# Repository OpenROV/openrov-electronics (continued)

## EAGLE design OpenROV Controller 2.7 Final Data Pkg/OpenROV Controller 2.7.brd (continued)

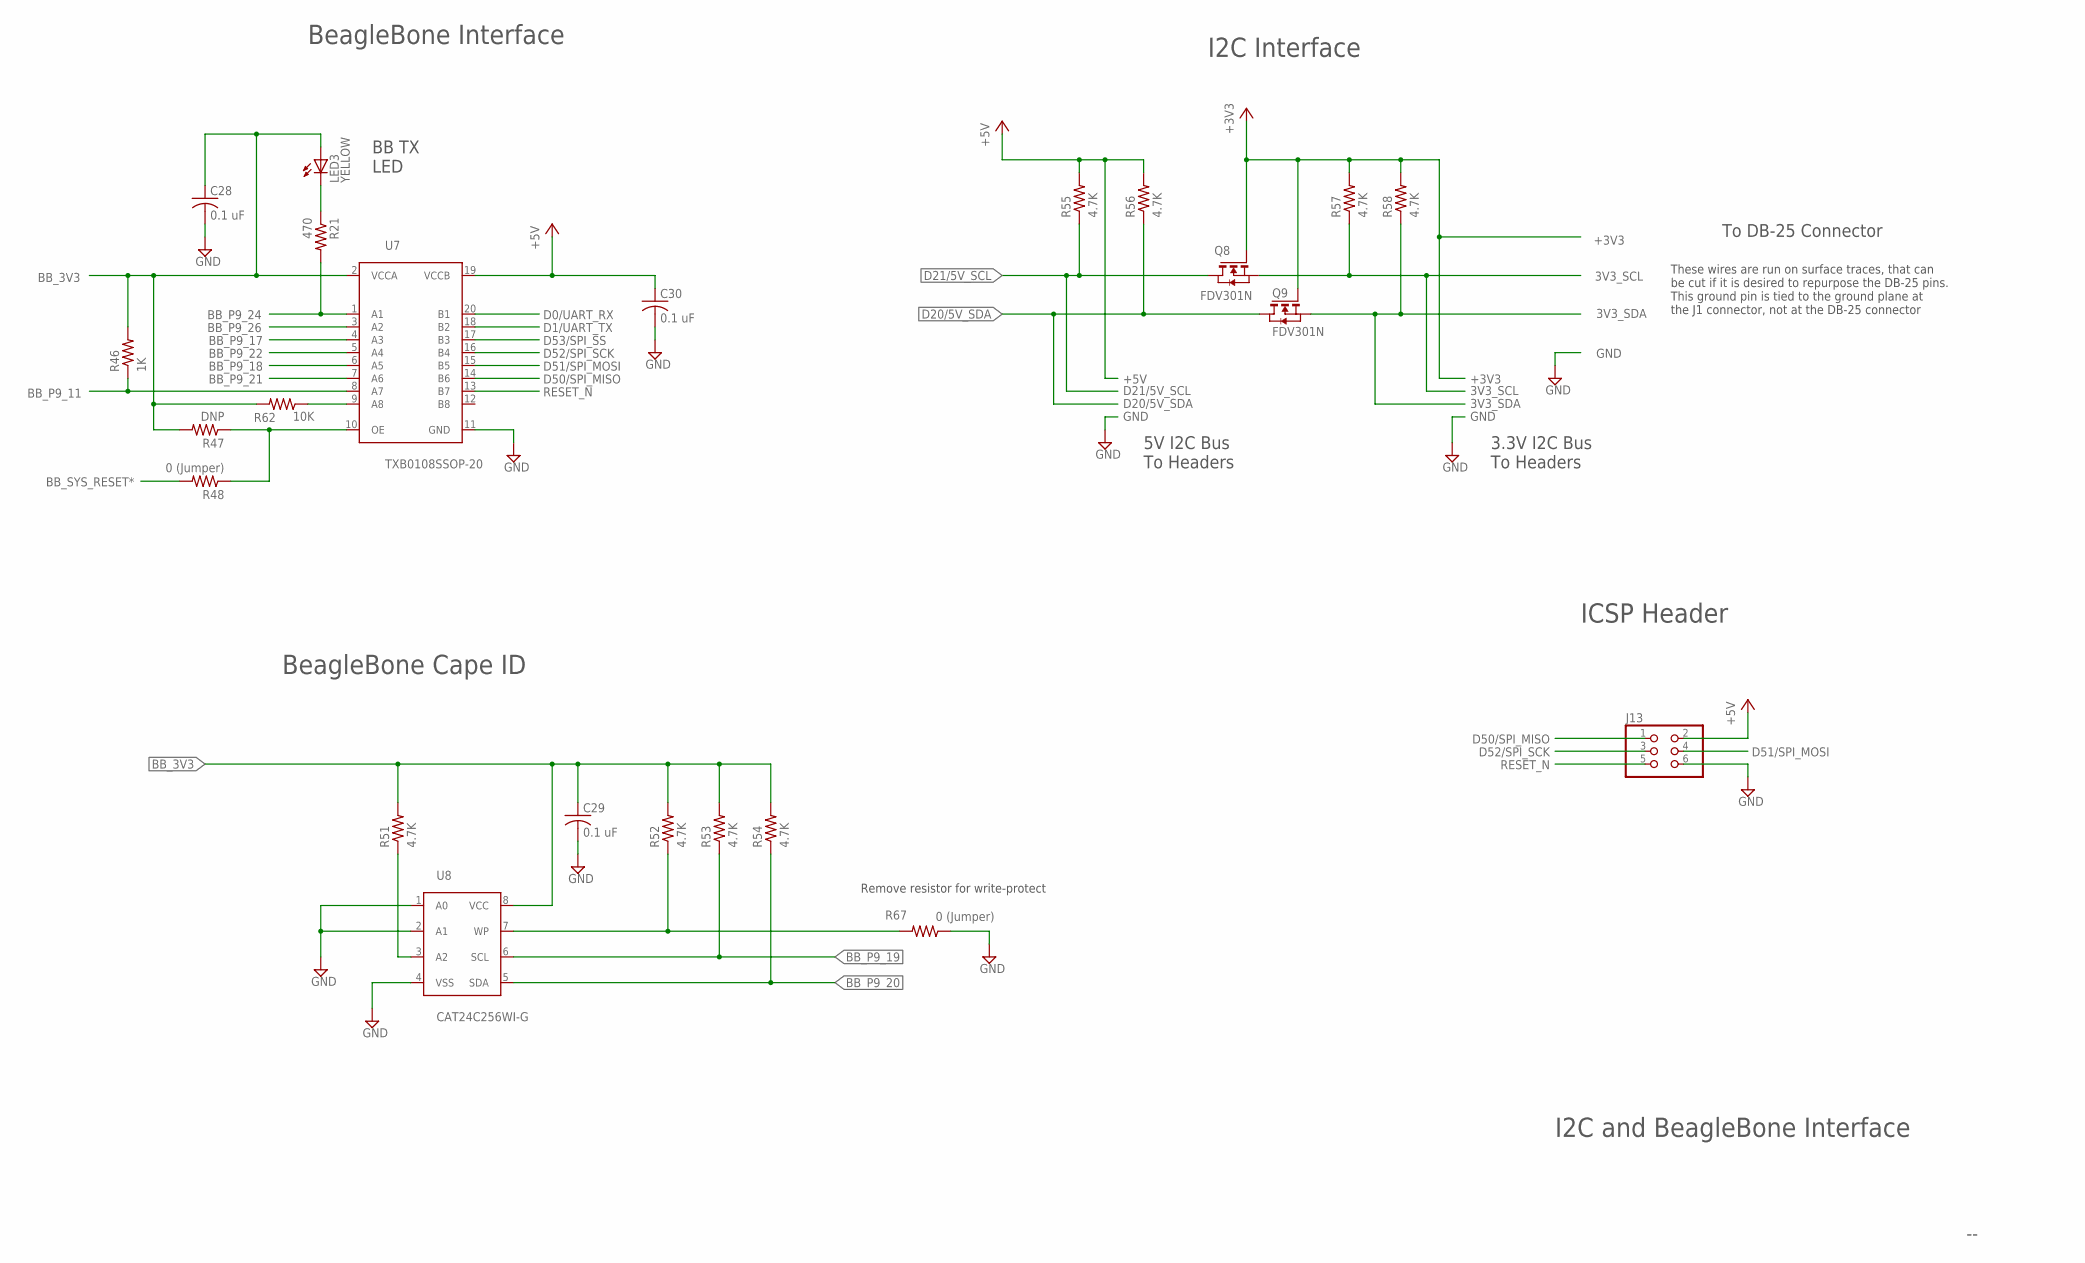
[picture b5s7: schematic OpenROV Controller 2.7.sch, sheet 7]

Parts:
C28, C29, C30: 0.1 uF; R0603
J13: HDR_PINS_2X3
LED3: YELLOW; LED_CHIPLED_0603
Q8, Q9: FDV301N; SOT23
R21: 470; R0603
R46: 1K; R0603
R47: DNP; R0603
R48, R67: 0 (Jumper); R0603
R51, R52, R53, R54, R55, R56, R57, R58: 4.7K; R0603
R62: 10K; R0603
U7: TXB0108SSOP-20; SSOP-20
U8: CAT24C256WI-G; SO8

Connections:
3V3_SCL: Q8.2 (S), R57.1; also elsewhere on the board
3V3_SDA: Q9.2 (S), R58.1; also elsewhere on the board
+3V3: Q8.1 (G), Q9.1 (G), R57.2, R58.2; also elsewhere on the board
+5V: C30.1, J13.2, R55.2, R56.2, U7.19 (VCCB); also elsewhere on the board
BB_3V3: C28.1, C29.1, LED3.A, R46.2, R47.2, R51.2, R52.2, R53.2, R54.2, R62.2, U7.2 (VCCA), U8.8 (VCC); also elsewhere on the board
BB_P9_11: R46.1, U7.8 (A7); also elsewhere on the board
BB_P9_17: U7.4 (A3); also elsewhere on the board
BB_P9_18: U7.6 (A5); also elsewhere on the board
BB_P9_19: R53.1, U8.6 (SCL); also elsewhere on the board
BB_P9_20: R54.1, U8.5 (SDA); also elsewhere on the board
BB_P9_21: U7.7 (A6); also elsewhere on the board
BB_P9_22: U7.5 (A4); also elsewhere on the board
BB_P9_24: R21.2, U7.1 (A1); also elsewhere on the board
BB_P9_26: U7.3 (A2); also elsewhere on the board
BB_SYS_RESET*: R48.2; also elsewhere on the board
D0/UART_RX: U7.20 (B1); also elsewhere on the board
D1/UART_TX: U7.18 (B2); also elsewhere on the board
D20/5V_SDA: Q9.3 (D), R56.1; also elsewhere on the board
D21/5V_SCL: Q8.3 (D), R55.1; also elsewhere on the board
D50/SPI_MISO: J13.1, U7.14 (B6); also elsewhere on the board
D51/SPI_MOSI: J13.4, U7.15 (B5); also elsewhere on the board
D52/SPI_SCK: J13.3, U7.16 (B4); also elsewhere on the board
D53/SPI_SS: U7.17 (B3); also elsewhere on the board
GND: C28.2, C29.2, C30.2, J13.6, R67.1, U7.11 (GND), U8.1 (A0), U8.2 (A1), U8.4 (VSS); also elsewhere on the board
unnamed: R47.1, R48.1, U7.10 (OE)
unnamed: R52.1, R67.2, U8.7 (WP)
unnamed: R51.1, U8.3 (A2)
unnamed: LED3.C, R21.1
unnamed: R62.1, U7.9 (A8)
RESET_N: J13.5, U7.13 (B7); also elsewhere on the board

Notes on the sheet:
I2C and BeagleBone Interface
I2C Interface
5V I2C Bus To Headers
3.3V I2C Bus To Headers
BeagleBone Interface
BeagleBone Cape ID
To DB-25 Connector
ICSP Header
These wires are run on surface traces, that can be cut if it is desired to repurpose the DB-25 pins. This ground pin is tied to the ground plane at the J1 connector, not at the DB-25 connector
Remove resistor for write-protect
BB TX LED

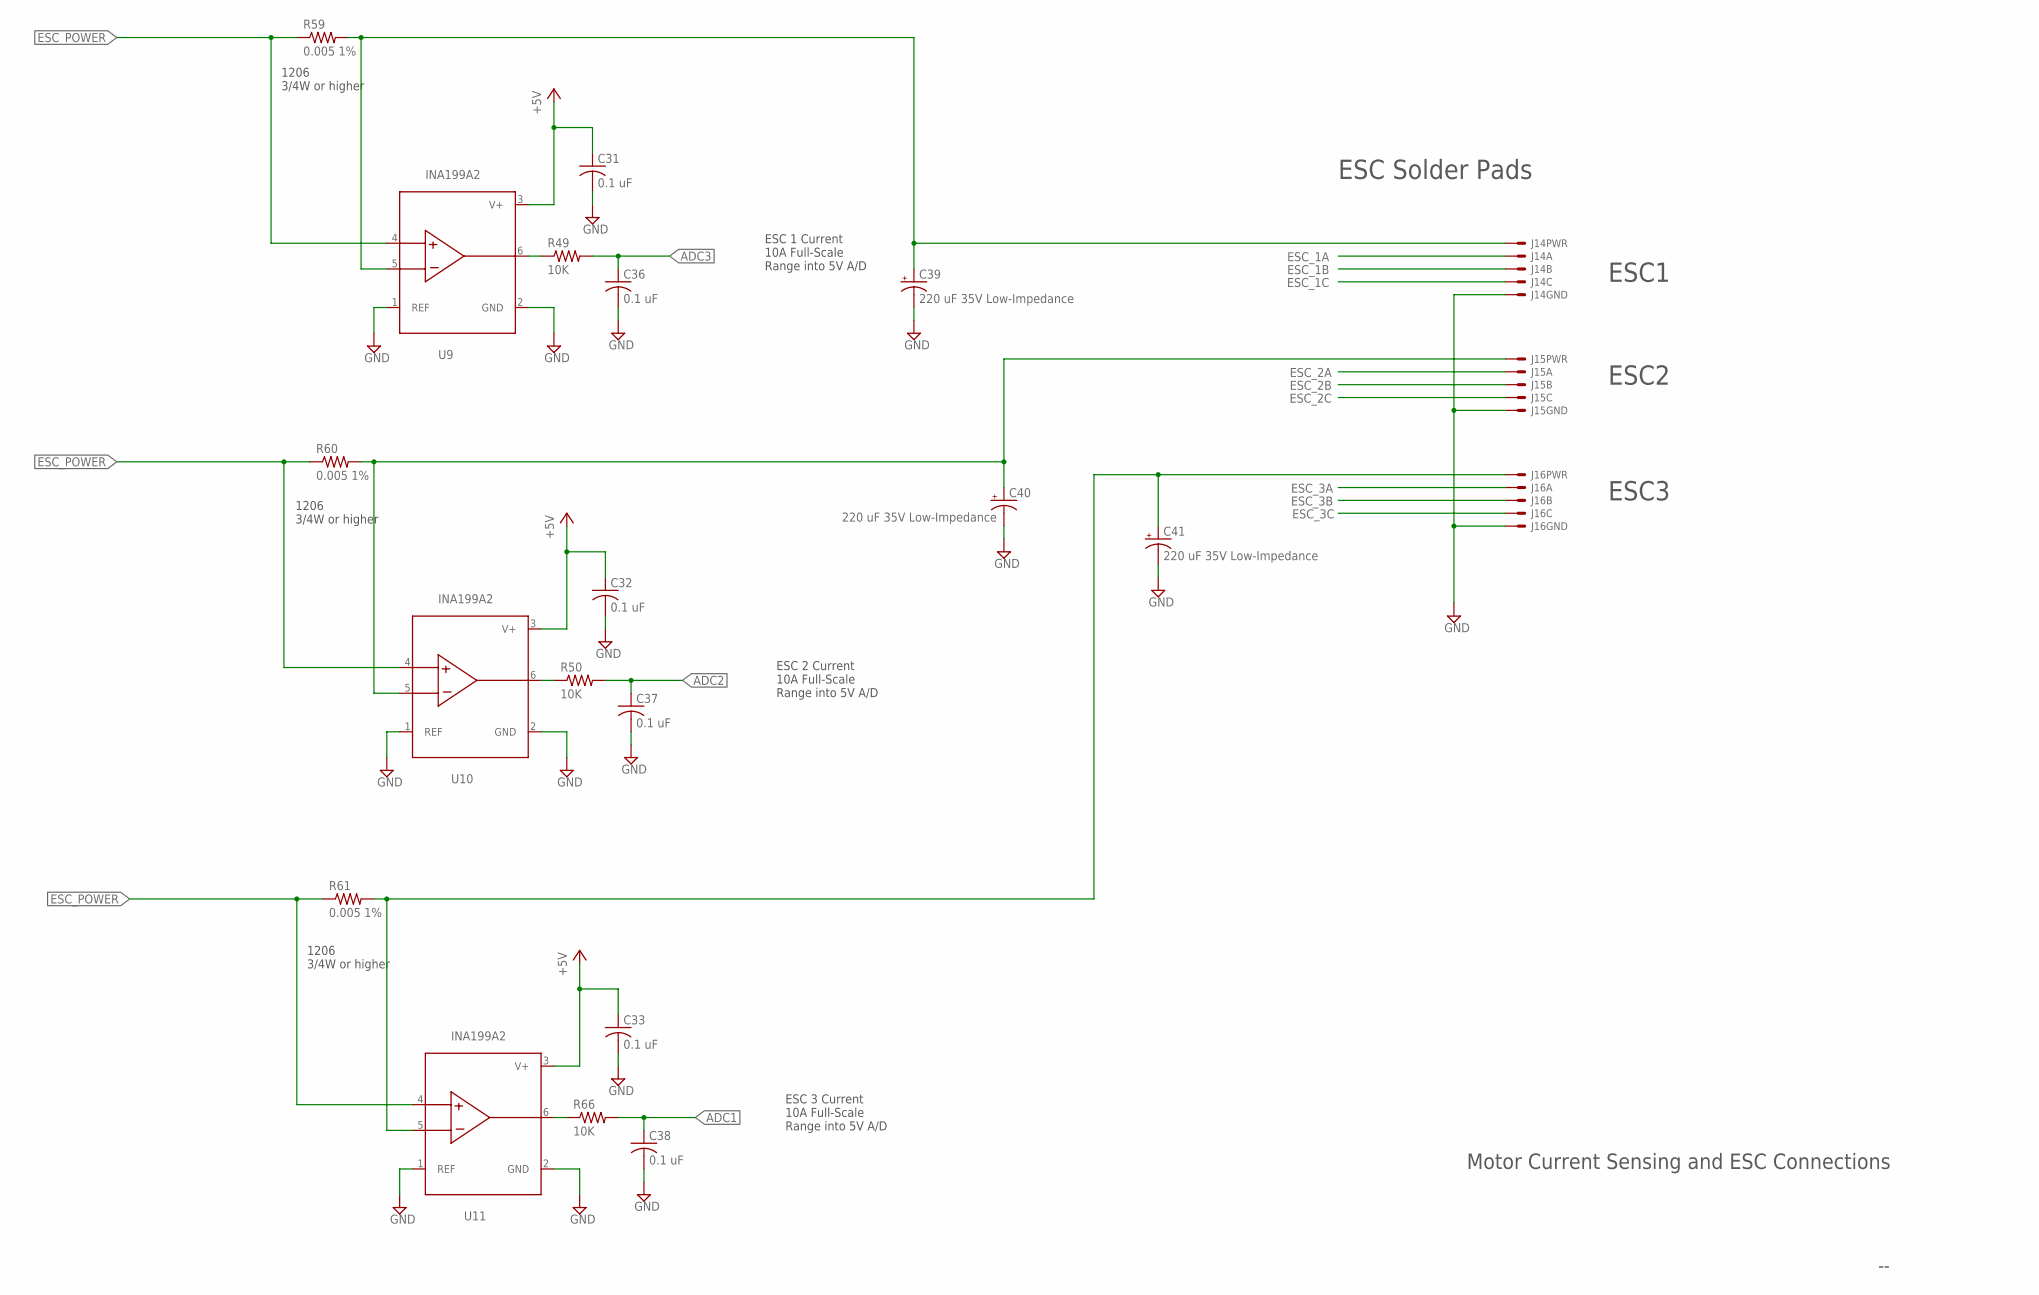
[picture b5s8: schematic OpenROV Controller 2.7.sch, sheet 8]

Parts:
C31, C32, C33, C36, C37, C38: 0.1 uF; R0603
C39, C40, C41: 220 uF 35V Low-Impedance; NICHICON_10MM
J14: ESC_PADS-AFRO-12/20A-ESC1; AFRO-ESC-12/20A-ESC1
J15: ESC_PADS-AFRO-12/20A-ESC2; AFRO-ESC-12/20A-ESC2
J16: ESC_PADS-AFRO-12/20A-ESC3; AFRO-ESC-12/20A-ESC3
R49, R50, R66: 10K; R0603
R59, R60, R61: 0.005 1%; R1206
U9, U10, U11: INA199A2; SC70-6L

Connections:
+5V: C31.1, C32.1, C33.1, U9.3 (V+), U10.3 (V+), U11.3 (V+); also elsewhere on the board
ADC1: C38.1, R66.2; also elsewhere on the board
ADC2: C37.1, R50.2; also elsewhere on the board
ADC3: C36.1, R49.2; also elsewhere on the board
ESC1_PWR: C39.+, J14.PWR1, J14.PWR2, R59.2, U9.5 (IN-)
ESC_1A: J14.A1, J14.A2; also elsewhere on the board
ESC_1B: J14.B1, J14.B2; also elsewhere on the board
ESC_1C: J14.C1, J14.C2; also elsewhere on the board
ESC_2A: J15.A1, J15.A2; also elsewhere on the board
ESC_2B: J15.B1, J15.B2; also elsewhere on the board
ESC_2C: J15.C1, J15.C2; also elsewhere on the board
ESC_3A: J16.A1, J16.A2; also elsewhere on the board
ESC_3B: J16.B1, J16.B2; also elsewhere on the board
ESC_3C: J16.C1, J16.C2; also elsewhere on the board
ESC_POWER: R59.1, R60.1, R61.1, U9.4 (IN+), U10.4 (IN+), U11.4 (IN+); also elsewhere on the board
ESC_PWR2: C40.+, J15.PWR1, J15.PWR2, R60.2, U10.5 (IN-)
ESC_PWR3: C41.+, J16.PWR1, J16.PWR2, R61.2, U11.5 (IN-)
GND: C31.2, C32.2, C33.2, C36.2, C37.2, C38.2, C39.-, C40.-, C41.-, J14.GND1, J14.GND2, J15.GND1, J15.GND2, J16.GND1, J16.GND2, U9.1 (REF), U9.2 (GND), U10.1 (REF), U10.2 (GND), U11.1 (REF), U11.2 (GND); also elsewhere on the board
unnamed: R49.1, U9.6 (VOUT)
unnamed: R50.1, U10.6 (VOUT)
unnamed: R66.1, U11.6 (VOUT)

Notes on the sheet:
Motor Current Sensing and ESC Connections
ESC Solder Pads
ESC1
ESC2
ESC3
1206 3/4W or higher
ESC 2 Current 10A Full-Scale Range into 5V A/D
ESC 1 Current 10A Full-Scale Range into 5V A/D
ESC 3 Current 10A Full-Scale Range into 5V A/D

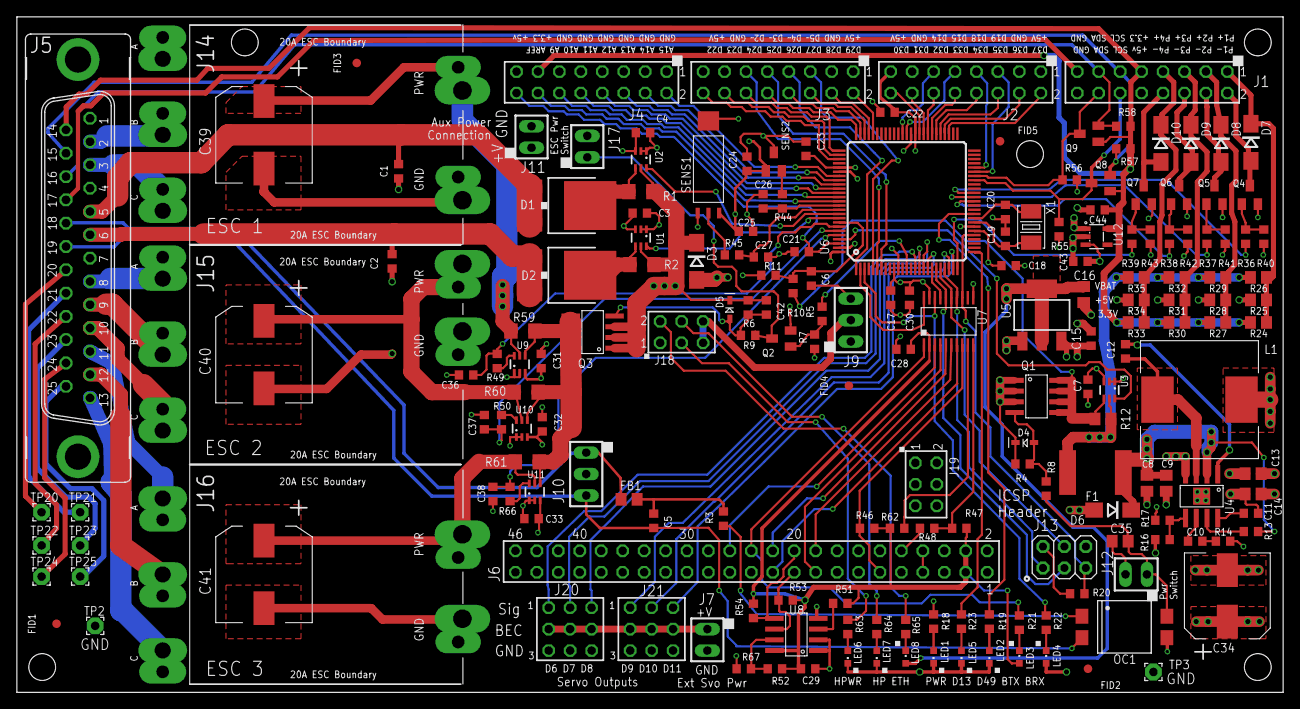
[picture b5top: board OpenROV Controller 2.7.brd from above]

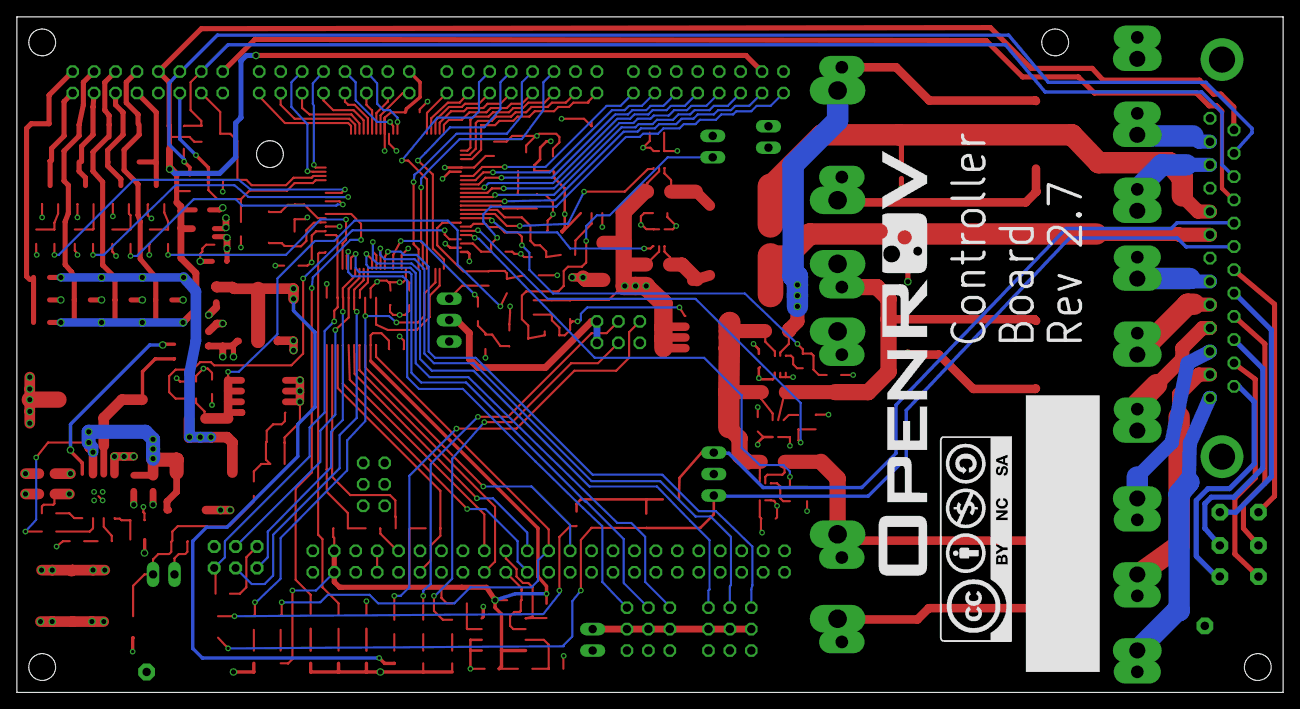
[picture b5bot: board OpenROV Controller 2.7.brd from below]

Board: 4 copper layers, 150.0 x 80.0 mm, 191 parts (2 on the bottom side), 159 nets.

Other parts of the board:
U$1: OROV-LOGO-2.00
U$2: CC-LOGO-1

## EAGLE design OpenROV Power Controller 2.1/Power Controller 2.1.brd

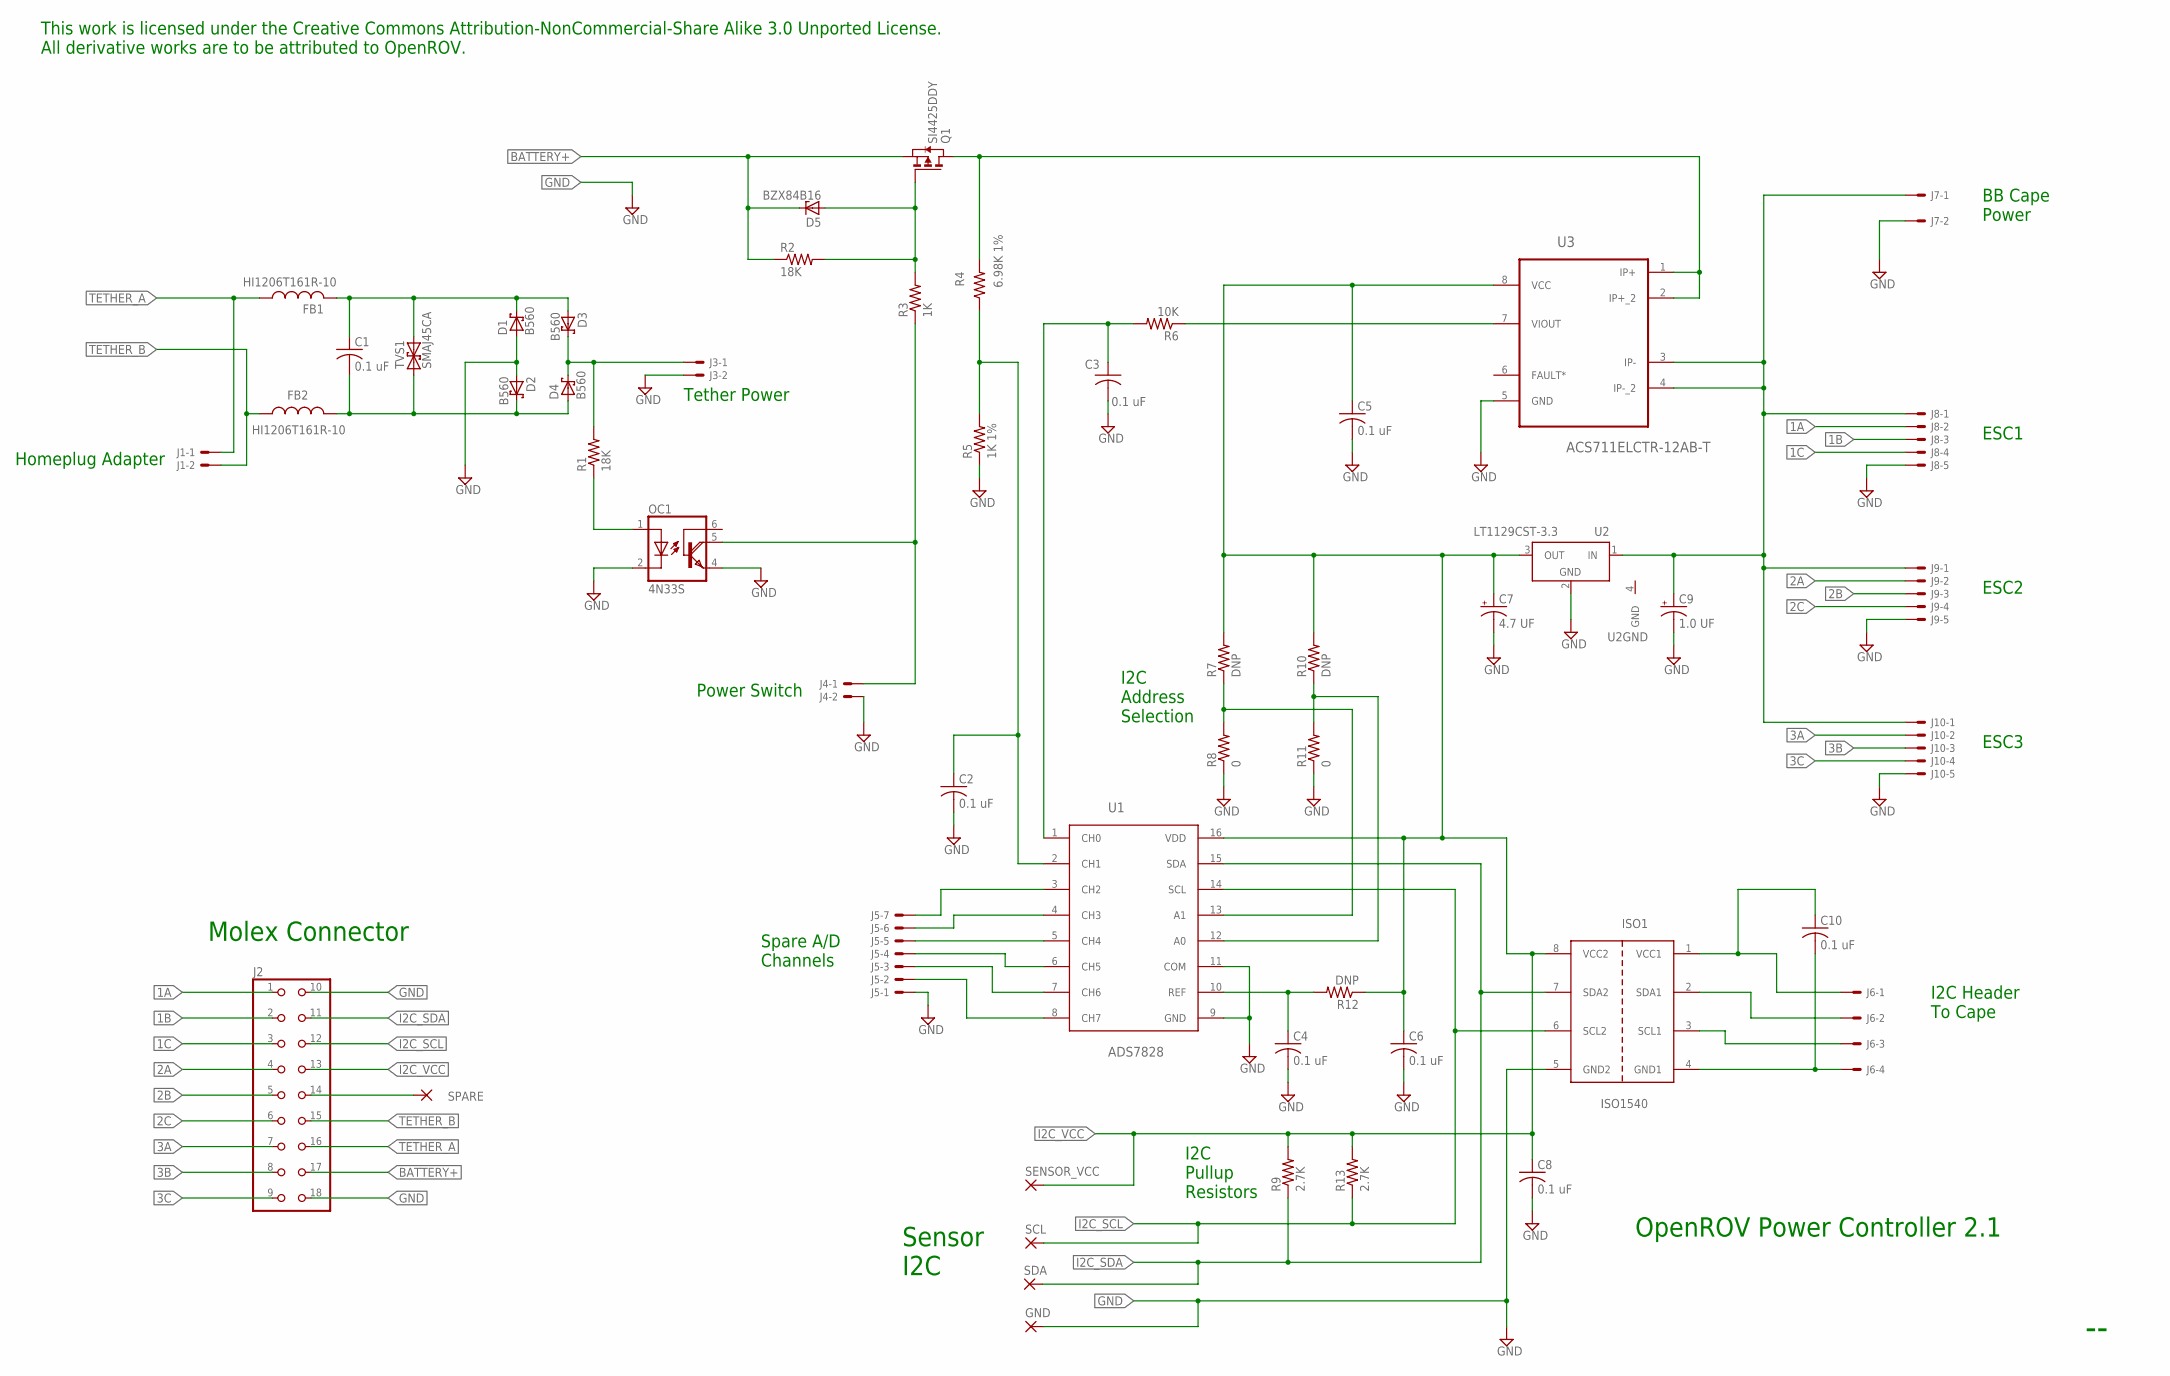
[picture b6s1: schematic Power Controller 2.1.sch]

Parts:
C1, C2, C3, C4, C5, C6, C8, C10: 0.1 uF; C0805K
C7: 4.7 UF; A/3216-18R
C9: 1.0 UF; A/3216-18R
D1, D2, D3, D4: B560; SMC
D5: BZX84B16; TO236
FB1, FB2: HI1206T161R-10; R1206
GND: 1,6/0,9
ISO1: ISO1540; SO8
J1, J4: 22-23-2021
J2: MINI-FIT-JR-18; MINI-FIT-JR-18-PEGS
J3, J7: KK-156-2
J5: 22-23-2071
J6: 22-23-2041
J8, J9, J10: ESC_PADSCUSTOM; ESC-PADS
OC1: 4N33S; DIL6-SMD
Q1: SI4425DDY; SO8
R1, R2: 18K; R0805
R3: 1K; R0805
R4: 6.98K 1%; R0805
R5: 1K 1%; R0805
R6: 10K; R0805
R7, R10, R12: DNP; R0805
R8, R11: 0; R0805
R9, R13: 2.7K; R0805
SCL: 1,6/0,9
SDA: 1,6/0,9
SENSOR_VCC: 1,6/0,9
SPARE: 1,6/0,9
TVS1: SMAJ45CA; DO214AC
U1: ADS7828; SSOP16
U2: LT1129CST-3.3; SOT223
U3: ACS711ELCTR-12AB-T; SOIC127P600X175-8N

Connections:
1A: J2.1, J8.2
1B: J2.2, J8.3
1C: J2.3, J8.4
2A: J2.4, J9.2
2B: J2.5, J9.3
2C: J2.6, J9.4
3A: J2.7, J10.2
3B: J2.8, J10.3
3C: J2.9, J10.4
BATTERY+: D5.C, J2.17, Q1.1 (S), Q1.2 (S), Q1.3 (S), R2.1
GND: C2.2, C3.2, C4.2, C5.2, C6.2, C7.-, C8.2, C9.-, D1.A, D2.A, GND.1, ISO1.5 (GND2), J2.10, J2.18, J3.2, J4.2, J5.1, J7.2, J8.5, J9.5, J10.5, OC1.2 (C), OC1.4 (E), R5.1, R8.1, R11.1, U1.9 (GND), U1.11 (COM), U2.2 (GND), U2.4 (GND), U3.5 (GND)
I2C_SCL: ISO1.6 (SCL2), J2.12, R13.1, SCL.1, U1.14 (SCL)
I2C_SDA: ISO1.7 (SDA2), J2.11, R9.1, SDA.1, U1.15 (SDA)
I2C_VCC: C5.1, C6.1, C7.+, C8.1, ISO1.8 (VCC2), J2.13, R7.2, R9.2, R10.2, R12.1, R13.2, SENSOR_VCC.1, U1.16 (VDD), U2.3 (OUT), U3.8 (VCC)
unnamed: J4.1, OC1.5 (COL), R3.1
unnamed: C10.2, ISO1.4 (GND1), J6.4
unnamed: ISO1.3 (SCL1), J6.3
unnamed: ISO1.2 (SDA1), J6.2
unnamed: C10.1, ISO1.1 (VCC1), J6.1
unnamed: J5.7, U1.3 (CH2)
unnamed: D5.A, Q1.4 (G), R2.2, R3.2
unnamed: C3.1, R6.2, U1.1 (CH0)
unnamed: J5.6, U1.4 (CH3)
unnamed: R7.1, R8.2, U1.13 (A1)
unnamed: R10.1, R11.2, U1.12 (A0)
unnamed: J5.5, U1.5 (CH4)
unnamed: J5.4, U1.6 (CH5)
unnamed: Q1.5 (D), Q1.6 (D), Q1.7 (D), Q1.8 (D), R4.2, U3.1 (IP+), U3.2 (IP+_2)
unnamed: C1.1, D1.C, D3.A, FB1.2, TVS1.C (2)
unnamed: C1.2, D2.C, D4.A, FB2.2, TVS1.A (1)
unnamed: OC1.1 (A), R1.1
unnamed: C2.1, R4.1, R5.2, U1.2 (CH1)
unnamed: J5.3, U1.7 (CH6)
unnamed: J5.2, U1.8 (CH7)
unnamed: C4.1, R12.2, U1.10 (REF)
unnamed: R6.1, U3.7 (VIOUT)
SPARE: J2.14, SPARE.1
TETHER_A: FB1.1, J1.1, J2.16
TETHER_B: FB2.1, J1.2, J2.15
TETHER_POWER: D3.C, D4.C, J3.1, R1.2
V_BAT_SWITCHED: C9.+, J7.1, J8.1, J9.1, J10.1, U2.1 (IN), U3.3 (IP-), U3.4 (IP-_2)

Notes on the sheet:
Homeplug Adapter
BB Cape Power
ESC1
ESC2
ESC3
Tether Power
OpenROV Power Controller 2.1
Molex Connector
I2C Header To Cape
Power Switch
Spare A/D Channels
This work is licensed under the Creative Commons Attribution-NonCommercial-Share Alike 3.0 Unported License. All derivative works are to be attributed to OpenROV.
I2C Address Selection
I2C Pullup Resistors
Sensor I2C

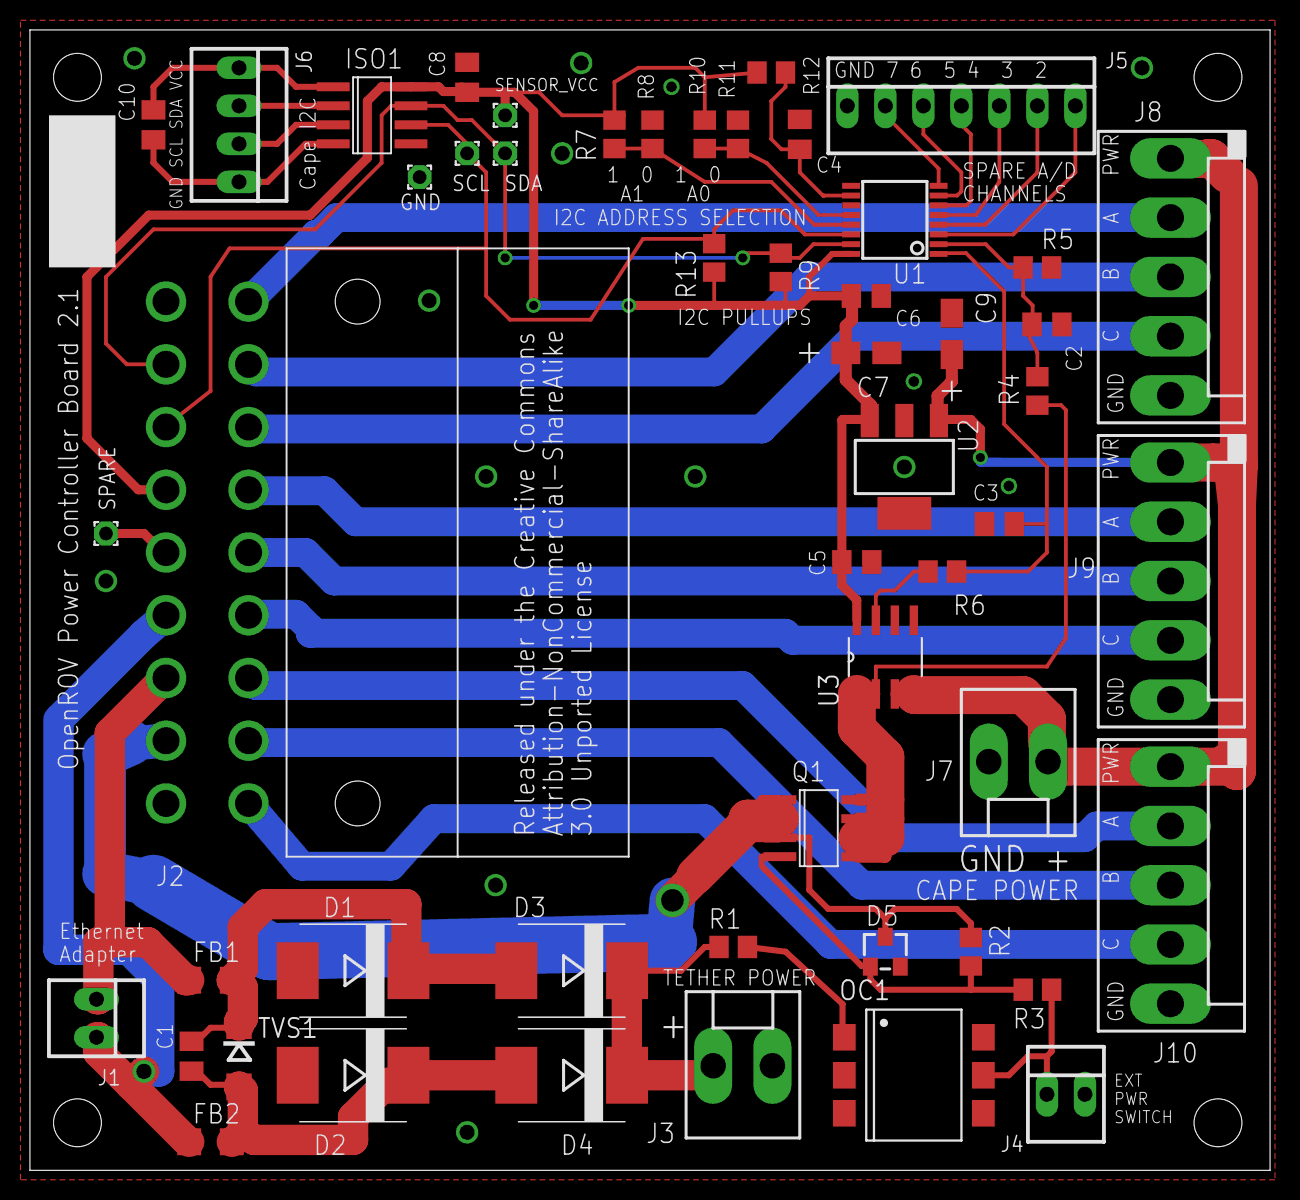
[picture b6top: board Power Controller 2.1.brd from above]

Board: 2 copper layers, 82.9 x 76.2 mm, 52 parts (0 on the bottom side), 41 nets.

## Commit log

2012-06-04 Added Eagle sch file for OpenROV BeagleBone Cape
2012-06-09 updated with correct BB RX resistor placement
2012-06-09 changed voltage divider for arduino to work
2012-06-09 started on new cape board
2012-06-11 start of PCB layout based on the adafruit cape
2012-06-12 removed the extra beagle board header pins to make more room for arduino pins
2012-06-12 swapped out IC1 for official sparkfun atmega328 footprint
2012-06-12 swapped out the giant crystal footprint for a smaller standard one with the same hole spacing
2012-06-12 moved servo headers back over to the right side of the board
2012-06-12 added headers for +9V and +12V
2012-07-10 OpenROV Cape with features for first proto build
    Added
    *Arduino headers for shield
    *Lights for Power, UART Tx/Rx, and pin 13
    *Header for FTDI programmer
    *Power FETs for higher power PWM output
    *Header for tilt servo
2012-07-24 Added values and fixed errors
    Added/ corrected values to most components, corrected erroneous voltage
    divider configuration to TX-O, added resister between BBTX and RX-I,
    changed sheet labels
2012-07-26 Disambiguated several features
2012-12-03 Removing old schematics and adding the new cape, both PDF design schematics and gerber files
2012-12-03 Remove warning from readme
2013-01-04 Added wiring schematics, based on current cape design
    Wiring schematics, based on current cape design.
    Drawn in CADInt (www.cadint.se)
2013-03-18 Files for power distribution board
2013-05-21 Updated schematics to suit V2.4
2013-05-21 Revert "Files for power distribution board"
    This reverts commit c7d6c21a26aa24c1f079386188f363bcc68efe48.
2013-08-02 added Power Control Board 2.1 schematics, gerbers and PDFs
2013-09-27 added OpenROV Controller v2.5B files, gerbers, schematics. Reorganized folders
2013-09-27 Update README.md
    Updated info about folders, v2.5
2013-09-27 Update README.md
    formatting
2014-01-30 Added first version of Controller Tester that went out to manufacturing
2014-02-01 Added Controller 2.6 files and Topside Adapter Board 2.6 files
2014-02-20 added image of test jig setup and software needed to test control boards
2014-03-27 added IMU tester board pictures, software, and text file with info.
2014-12-17 Added 2.7 Controllerboard and the light board
2015-09-18 Added 2.8 Files
    2.8 Control Board Final Data Package, 2.8 Light Board Final Data Package
2015-09-23 Added IMU/Depth Module v2
    Data Package for IMU/Depth Module v2
2015-11-24 Added Light Board 2.8A Data Package
2015-11-24 Added External Light Cube Package
2015-12-09 BOM Rev 1 added
    Changed the LED to a more efficient one.
2016-03-16 Added 2.6A Data Package
2022-01-22 README Refactor
2022-08-11 Formatted README
